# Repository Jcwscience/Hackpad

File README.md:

# Hackpad
A tablet designed from scratch to be open and repairable.

## Current hardware core (Nvidia Jetson Xavier NX Dev-Kit)

### Feature Wishlist

* SDR Transciever
* 4k Camera
* NVME SSD
* NFC
* Linux
* Offline voice assistant
* GPS
* Multi carrier LTE
* Bluetooth 5.2
* Wifi-AX
* GPIO
* Hardware kill switches
* Full encryption
* Standard and e-ink displays
* Fingerprint scanner
* External antenna support

### Current Parts List
12x - Samsung 35-E 18650 Lithium-Ion

3S 11.1V 12.6V 25A W/Balance... https://www.amazon.com/dp/B075D96HVV?ref=ppx_pop_mob_ap_share

HiLetgo 3pcs XL4015 5A DC to DC... https://www.amazon.com/dp/B01EQT63SS?ref=ppx_pop_mob_ap_share

EVICIV 12.3’’ Raspberry Pi... https://www.amazon.com/dp/B08P1M54G6?ref=ppx_pop_mob_ap_share

Gravity: INA219 I2C Digital... https://www.amazon.com/dp/B07N3QQ2Q7?ref=ppx_pop_mob_ap_share

Spot Welder, Kerpu Mini Spot... https://www.amazon.com/dp/B092DB5R3S?ref=ppx_pop_mob_ap_share

waveshare SIM7600G-H... https://www.amazon.com/dp/B085MJD742?ref=ppx_pop_mob_ap_share

ACEIRMC 2pcs INMP441... https://www.amazon.com/dp/B09222JFBX?ref=ppx_pop_mob_ap_share

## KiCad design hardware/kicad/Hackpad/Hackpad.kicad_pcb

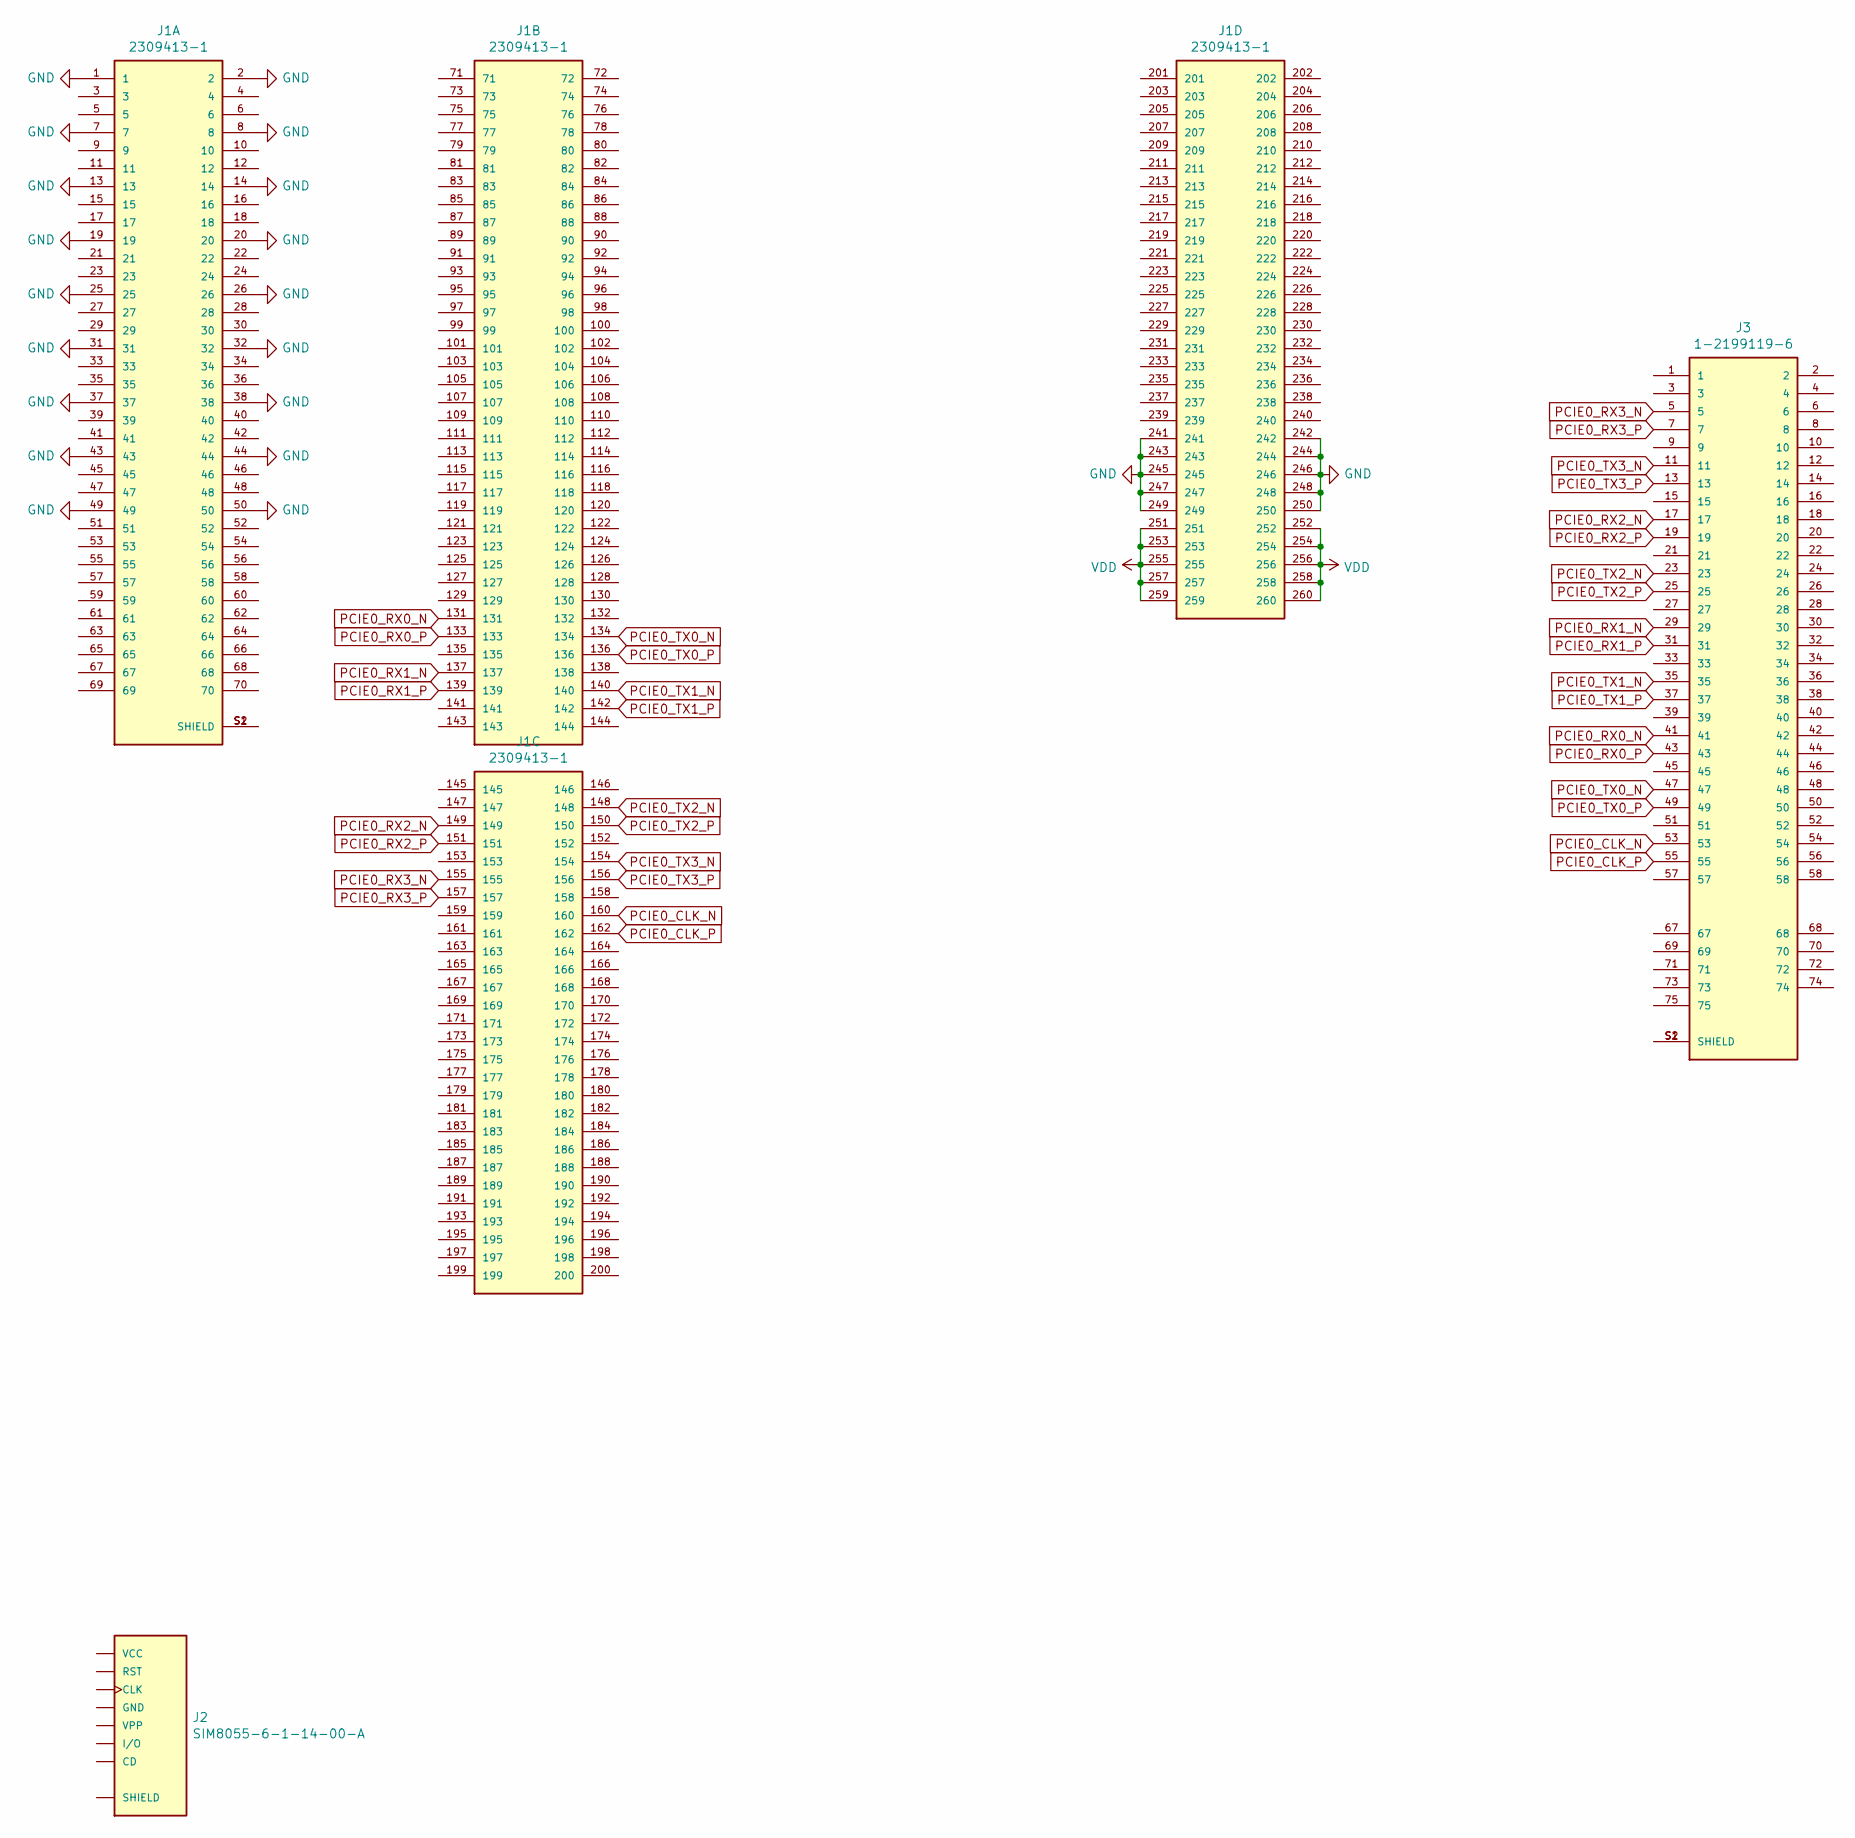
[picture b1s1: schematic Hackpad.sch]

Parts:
J1: 2309413-1; TE_2309413-1
J2: SIM8055-6-1-14-00-A; GCT_SIM8055-6-1-14-00-A; PARTREV A1
J3: 1-2199119-6; TE_1-2199119-6

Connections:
GND: J1.1, J1.2, J1.7, J1.8, J1.13, J1.14, J1.19, J1.20, J1.25, J1.26, J1.31, J1.32, J1.37, J1.38, J1.43, J1.44, J1.49, J1.50, J1.241, J1.242, J1.243, J1.244, J1.245, J1.246, J1.247, J1.248, J1.249, J1.250
unnamed: J1.S1 (SHIELD), J1.S2 (SHIELD)
unnamed: J2.C4 (SHIELD), J2.C8 (SHIELD)
unnamed: J3.S1 (SHIELD), J3.S2 (SHIELD)
PCIE0_CLK_N: J1.160, J3.53
PCIE0_CLK_P: J1.162, J3.55
PCIE0_RX0_N: J1.131, J3.41
PCIE0_RX0_P: J1.133, J3.43
PCIE0_RX1_N: J1.137, J3.29
PCIE0_RX1_P: J1.139, J3.31
PCIE0_RX2_N: J1.149, J3.17
PCIE0_RX2_P: J1.151, J3.19
PCIE0_RX3_N: J1.155, J3.5
PCIE0_RX3_P: J1.157, J3.7
PCIE0_TX0_N: J1.134, J3.47
PCIE0_TX0_P: J1.136, J3.49
PCIE0_TX1_N: J1.140, J3.35
PCIE0_TX1_P: J1.142, J3.37
PCIE0_TX2_N: J1.148, J3.23
PCIE0_TX2_P: J1.150, J3.25
PCIE0_TX3_N: J1.154, J3.11
PCIE0_TX3_P: J1.156, J3.13
VDD: J1.251, J1.252, J1.253, J1.254, J1.255, J1.256, J1.257, J1.258, J1.259, J1.260

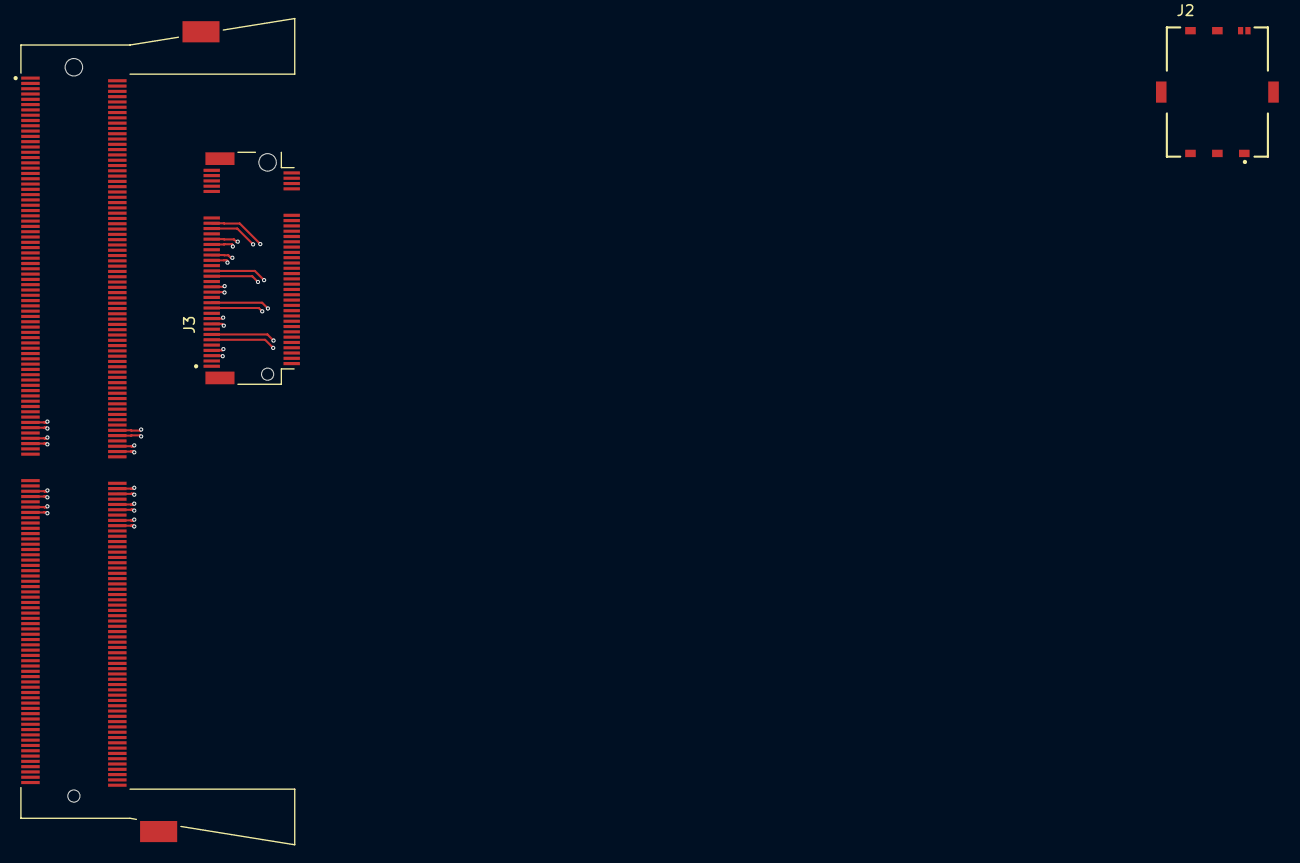
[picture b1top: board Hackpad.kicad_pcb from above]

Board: 4 copper layers, 3 parts (0 on the bottom side), 23 nets.

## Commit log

2021-08-27 Add Hardware Directory
